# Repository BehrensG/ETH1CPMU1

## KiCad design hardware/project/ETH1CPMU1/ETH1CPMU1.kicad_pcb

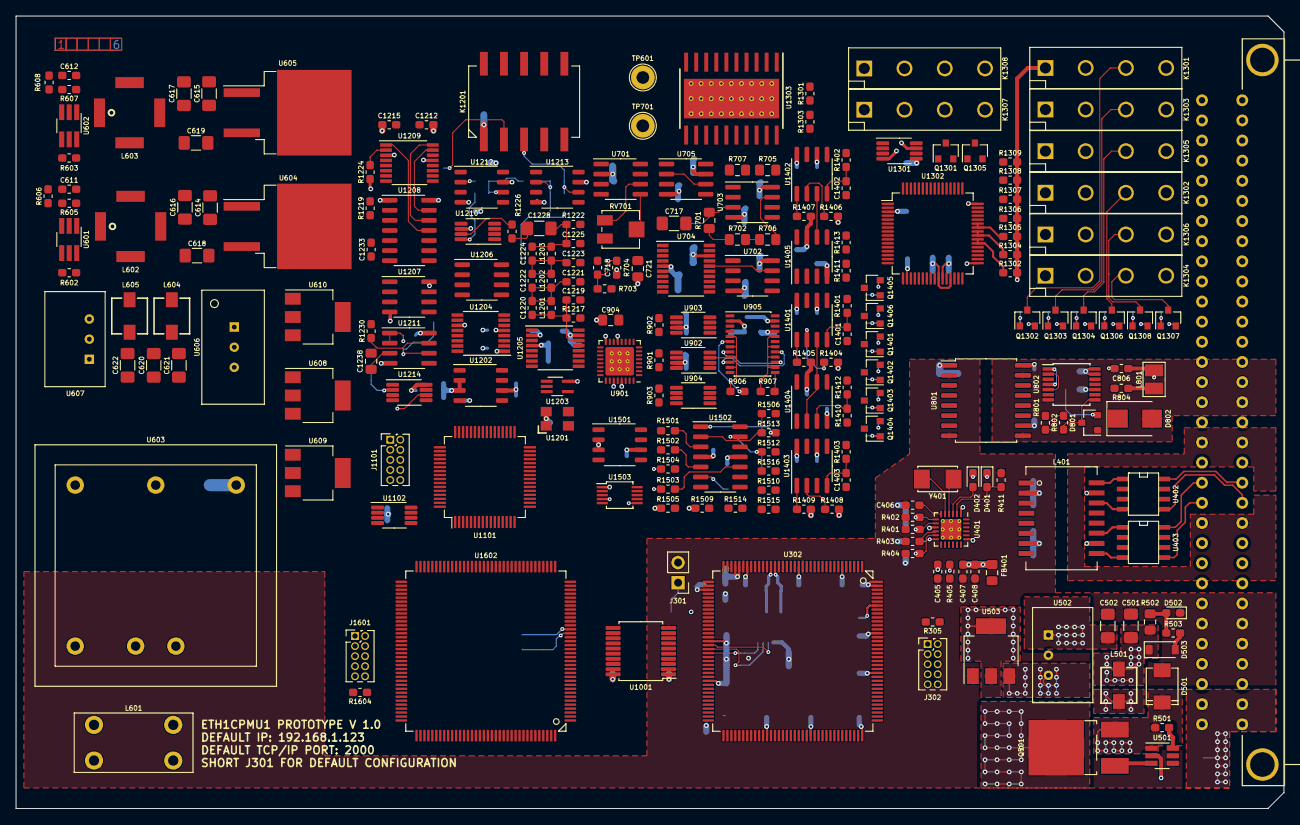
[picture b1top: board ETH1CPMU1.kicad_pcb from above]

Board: 6 copper layers, 160.0 x 100.0 mm, 532 parts (0 on the bottom side), 380 nets.

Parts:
C301, C302, C303, C305, C308, C310, C312, C313, C314, C315, C316, C317, C318, C319, C321, C402, C405, C408, C409, C410, C411, C412, C703, C704, C707, C708, C711, C712, C715, C716, C718, C720, C722, C801, C803, C805, C901, C902, C905, C906, C909, C911, C913, C1001, C1002, C1101, C1102, C1103, C1104, C1105, C1106, C1107, C1109, C1201, C1203, C1204, C1206, C1207, C1208, C1209, C1210, C1212, C1213, C1215, C1216, C1218, C1226, C1227, C1229, C1230, C1231, C1234, C1243, C1301, C1303, C1305, C1310, C1311, C1312, C1316, C1318, C1404, C1405, C1406, C1407, C1408, C1409, C1416, C1417, C1418, C1419, C1501, C1503, C1504, C1601, C1603, C1605, C1608, C1609, C1611, C1612, C1613, C1614, C1615, C1616, C1617, C1619: 100n; C_0603_1608Metric_Pad1.05x0.95mm_HandSolder
C304, C306, C401, C404, C1110, C1111, C1602, C1604: 8p; C_0603_1608Metric_Pad1.05x0.95mm_HandSolder
C307, C309, C1108, C1238, C1606, C1607: 2u2; C_0805_2012Metric_Pad1.15x1.40mm_HandSolder
C311, C320, C406, C407, C605, C606, C802, C804, C1205, C1505, C1610, C1618: 1u; C_0603_1608Metric_Pad1.05x0.95mm_HandSolder
C403, C1233: 470p; C_0603_1608Metric_Pad1.05x0.95mm_HandSolder
C413, C414: 1n/1kV; C_1206_3216Metric_Pad1.42x1.75mm_HandSolder
C501, C502, C620, C621, C622, C623, C624, C625: 10u/50V; C_1206_3216Metric_Pad1.42x1.75mm_HandSolder
C503, C504, C626, C627, C628, C629, C630: 10u/16V; C_1206_3216Metric_Pad1.42x1.75mm_HandSolder
C601, C602, C603, C604, C613, C614, C616, C618, C619: 4u7/50V; C_1206_3216Metric_Pad1.42x1.75mm_HandSolder
C607, C608: 1u/HC; C_1206_3216Metric_Pad1.42x1.75mm_HandSolder
C609, C610: 330p/2kV; C_1206_3216Metric_Pad1.42x1.75mm_HandSolder
C611, C612, C1220: 4p7; C_0603_1608Metric_Pad1.05x0.95mm_HandSolder
C615, C617: 2u2/50V; C_1206_3216Metric_Pad1.42x1.75mm_HandSolder
C701, C702, C705, C706, C709, C710, C713, C714, C719, C721, C903, C904, C907, C908, C910, C912, C917, C1202, C1302, C1304, C1309, C1315, C1317, C1502: 10u; C_0805_2012Metric_Pad1.15x1.40mm_HandSolder
C717, C1228: 10u; C_1206_3216Metric_Pad1.42x1.75mm_HandSolder
C806: 47p; C_0603_1608Metric_Pad1.05x0.95mm_HandSolder
C914, C915, C916, C1217, C1237, C1244, C1307, C1510, C1511, C1512, C1513: 1n; C_0603_1608Metric_Pad1.05x0.95mm_HandSolder
C1211, C1506, C1507, C1508, C1509: 220n; C_0603_1608Metric_Pad1.05x0.95mm_HandSolder
C1214: 10n; C_0603_1608Metric_Pad1.05x0.95mm_HandSolder
C1219, C1225: 22p; C_0603_1608Metric_Pad1.05x0.95mm_HandSolder
C1221, C1223: 56p; C_0603_1608Metric_Pad1.05x0.95mm_HandSolder
C1222: 18p; C_0603_1608Metric_Pad1.05x0.95mm_HandSolder
C1224: 12p; C_0603_1608Metric_Pad1.05x0.95mm_HandSolder
C1232, C1239, C1313, C1314, C1401, C1402, C1403: C; C_0603_1608Metric_Pad1.05x0.95mm_HandSolder
C1235: 330p; C_0603_1608Metric_Pad1.05x0.95mm_HandSolder
C1236: 220p; C_0603_1608Metric_Pad1.05x0.95mm_HandSolder
C1240: 150p; C_0603_1608Metric_Pad1.05x0.95mm_HandSolder
C1241: 4n7; C_0603_1608Metric_Pad1.05x0.95mm_HandSolder
C1242, C1319, C1320, C1321, C1322, C1323, C1324, C1325, C1326, C1410, C1411, C1412, C1413, C1414, C1415: 10p; C_0603_1608Metric_Pad1.05x0.95mm_HandSolder
C1306: 100p; C_0603_1608Metric_Pad1.05x0.95mm_HandSolder
C1308: 3n3; C_0603_1608Metric_Pad1.05x0.95mm_HandSolder
D401: YELLOW; LED_0603_1608Metric_Pad1.05x0.95mm_HandSolder
D402: GREEN; LED_0603_1608Metric_Pad1.05x0.95mm_HandSolder
D501: SM6T30AY; DO_214AA_REV
D502: RED; LED_0603_1608Metric_Pad1.05x0.95mm_HandSolder
D503: MMSZ5249B; D_SOD-123
D601, D602: PMEG6010CEJ; D_SOD-323_HandSoldering
D801: BAV99; SOT-23
D802: SMBJ5.0A; D_SMB
D803: SD36C-01FTG; D_SOD-323_HandSoldering
D1201: SD103ATW; SOT-363_SC-70-6
D1202: 1N4148W; D_SOD-123
F501: MF-LSMF185/33X; Fuse_SMD2920
FB301, FB401, FB1601: 742792031; L_0805_2012Metric_Pad1.15x1.40mm_HandSolder
J201: C64AC; Socket_DIN41612-CaseC1-AC-Male-64Pin-2rows
J301: Conn_02x01; PinHeader_1x02_P2.54mm_Vertical
J302, J1101, J1601: Conn_02x05; PinHeader_2x05_P1.27mm_Vertical
K1201: TQ2SA-5V; SA
K1301, K1302, K1303, K1304, K1305, K1306, K1307, K1308: HE3621A0510; HE360_x-5050462-8
L401: 749010012A
L501, L604, L605: TCK-141
L601: 7448013501
L602, L603: 74489440068
L801: CW252016-R33G; CW252016
L1201, L1202, L1203: 4u7; L_0603_1608Metric_Pad1.05x0.95mm_HandSolder
Q501: IRFR5410; TO-252-2_Rectifier
Q1201, Q1301, Q1302, Q1303, Q1304, Q1305, Q1306, Q1307, Q1308, Q1401, Q1402, Q1403, Q1404, Q1405, Q1406: BC847; SOT-23
R301, R302, R1101, R1102, R1601, R1602: 4k7; R_0603_1608Metric_Pad1.05x0.95mm_HandSolder
R303, R304, R305, R403, R406, R407, R408, R409, R411, R704, R1103, R1104, R1201, R1205, R1209, R1219, R1221, R1223, R1224, R1225, R1227, R1228, R1229, R1230, R1233, R1241, R1242, R1243, R1244, R1310, R1311, R1312, R1313, R1314, R1315, R1316, R1317, R1414, R1415, R1416, R1417, R1418, R1419, R1603, R1604: 10k; R_0603_1608Metric_Pad1.05x0.95mm_HandSolder
R401, R402, R404, R405: 33; R_0603_1608Metric_Pad1.05x0.95mm_HandSolder
R410: 1k5; R_0603_1608Metric_Pad1.05x0.95mm_HandSolder
R412: 12k1; R_0603_1608Metric_Pad1.05x0.95mm_HandSolder
R413, R414: 270; R_0603_1608Metric_Pad1.05x0.95mm_HandSolder
R415, R416, R417, R418: 49R9; R_0603_1608Metric_Pad1.05x0.95mm_HandSolder
R419: 1M/1kV; R_1206_3216Metric_Pad1.42x1.75mm_HandSolder
R420, R421: 75/1%; R_0603_1608Metric_Pad1.05x0.95mm_HandSolder
R501, R1216, R1404, R1405, R1406, R1407, R1408, R1409, R1412, R1413, R1513, R1514, R1515, R1516: 100k; R_0603_1608Metric_Pad1.05x0.95mm_HandSolder
R502: 6k8/0.5W; R_0805_2012Metric_Pad1.15x1.40mm_HandSolder
R503: 370; R_0603_1608Metric_Pad1.05x0.95mm_HandSolder
R601, R603, R605, R607: 1M; R_0603_1608Metric_Pad1.05x0.95mm_HandSolder
R602, R604: 287k; R_0603_1608Metric_Pad1.05x0.95mm_HandSolder
R606, R608, R1202, R1203, R1204, R1226, R1231, R1236, R1237, R1239, R1309, R1401, R1402, R1403: R; R_0603_1608Metric_Pad1.05x0.95mm_HandSolder
R701: 1k5/0.01%/0.6ppm; R_0805_2012Metric_Pad1.15x1.40mm_HandSolder
R702, R705, R707: 1k/0.01%/0.6ppm; R_0805_2012Metric_Pad1.15x1.40mm_HandSolder
R703, R904, R905, R906, R907, R1206, R1218: 0; R_0603_1608Metric_Pad1.05x0.95mm_HandSolder
R706: 2k/0.01%/0.6ppm; R_0805_2012Metric_Pad1.15x1.40mm_HandSolder
R801: 14k7; R_0603_1608Metric_Pad1.05x0.95mm_HandSolder
R802, R901, R902, R903: 100; R_0603_1608Metric_Pad1.05x0.95mm_HandSolder
R803, R1212, R1501, R1502, R1503, R1504: 1k; R_0603_1608Metric_Pad1.05x0.95mm_HandSolder
R804: 47; R_0603_1608Metric_Pad1.05x0.95mm_HandSolder
R805: 51R1; R_0603_1608Metric_Pad1.05x0.95mm_HandSolder
R1207: 4k22; R_0603_1608Metric_Pad1.05x0.95mm_HandSolder
R1208, R1213: 3k9; R_0603_1608Metric_Pad1.05x0.95mm_HandSolder
R1210, R1211: 1k96; R_0603_1608Metric_Pad1.05x0.95mm_HandSolder
R1214, R1505, R1507, R1509, R1511: 24k9; R_0603_1608Metric_Pad1.05x0.95mm_HandSolder
R1215, R1506, R1508, R1510, R1512: 33k2; R_0603_1608Metric_Pad1.05x0.95mm_HandSolder
R1217, R1222: 300; R_0603_1608Metric_Pad1.05x0.95mm_HandSolder
R1220: 70k; R_0603_1608Metric_Pad1.05x0.95mm_HandSolder
R1232, R1235, R1238: 6k81; R_0603_1608Metric_Pad1.05x0.95mm_HandSolder
R1234: 237k; R_0603_1608Metric_Pad1.05x0.95mm_HandSolder
R1240: 619; R_0603_1608Metric_Pad1.05x0.95mm_HandSolder
R1301, R1303: 5k1; R_0603_1608Metric_Pad1.05x0.95mm_HandSolder
R1302: 124k; R_0603_1608Metric_Pad1.05x0.95mm_HandSolder
R1304: 12k4; R_0603_1608Metric_Pad1.05x0.95mm_HandSolder
R1305: 1k24; R_0603_1608Metric_Pad1.05x0.95mm_HandSolder
R1306: 124; R_0603_1608Metric_Pad1.05x0.95mm_HandSolder
R1307: 12R4; R_0603_1608Metric_Pad1.05x0.95mm_HandSolder
R1308: 3R16; R_0603_1608Metric_Pad1.05x0.95mm_HandSolder
R1410, R1411: 50; R_0603_1608Metric_Pad1.05x0.95mm_HandSolder
RV701: 3314J-1-103E; Potentiometer_Bourns_3314J_Vertical
TP601, TP701: 5006; TestPoint_Loop_D2.60mm_Drill1.6mm_Beaded
U301, U1102, U1601: 24LC08B-E/MS; MSOP-8_3x3mm_P0.65mm
U302: STM32F765ZGT6; TQFP-144_20x20mm_P0.5mm
U401: LAN8742A; QFN-24-1EP_4x4mm_P0.5mm_EP2.6x2.6mm_ThermalVias
U402, U403: LC03-3.3; SO8E
U501: MAX5902; SOT-23-6_Handsoldering
U502: TSR1-2450; TSR1
U503, U608, U609: LM1117IMP-3.3/NOPB; SOT-223-3_TabPin2
U601, U602: LT8330_S6; TSOT-23-6_HandSoldering
U603: THL15-2415WI; THL15
U604: MC7815BD2TG; TO-263-2
U605: MC7915BD2TG; TO-263-2
U606: TSR2-2450; TSR2
U607: TSR1-2490; TSR1
U610: LM1117IMP-5.0/NOPB; SOT-223-3_TabPin2
U701: REF02AU; SOIC-8_3.9x4.9mm_P1.27mm
U702, U703: AD8676; SOIC-8_3.9x4.9mm_P1.27mm
U704: AD5791; TSSOP-20_4.4x6.5mm_P0.65mm
U705: AD8675; SOIC-8_3.9x4.9mm_P1.27mm
U801: ADuM5402; SOIC-16W_7.5x10.3mm_P1.27mm
U802: 74AC125; TSSOP-14_4.4x5mm_P0.65mm
U901: ADS8363; QFN-32-1EP_5x5mm_P0.5mm_EP3.6x3.6mm_ThermalVias
U902, U903, U904: INA159; MSOP-8_3x3mm_P0.65mm
U905: ADG1414BRU; TSSOP-24_4.4x7.8mm_P0.65mm
U1001: ADuM3151; SSOP-20_5.3x7.2mm_P0.65mm
U1101: STM32F413RGT6Tx; LQFP-64_10x10mm_P0.5mm
U1201: ECS-3225SMV-500-GP-TR; ECS
U1202, U1501: REF192; SSOP-8_3.9x5.05mm_P1.27mm
U1203: 74AHCT1G08; SOT-353_SC-70-5_Handsoldering
U1204: AD5689BRUZ; TSSOP-16_4.4x5mm_P0.65mm
U1205: AD9835; TSSOP-16_4.4x5mm_P0.65mm
U1206, U1207, U1211: TL072; SOIC-8_3.9x4.9mm_P1.27mm
U1208: TXB0104D; SOIC-14_3.9x8.7mm_P1.27mm
U1209: DG408DY; TSSOP-16_4.4x5mm_P0.65mm
U1210: AD5453YRMZ; MSOP-8_3x3mm_P0.65mm
U1212, U1213: LT1468; SSOP-8_3.9x5.05mm_P1.27mm
U1214: ADS7818; MSOP-8_3x3mm_P0.65mm
U1301: DG419LEUA; MSOP-8_3x3mm_P0.65mm
U1302: AD5520; LQFP-64_10x10mm_P0.5mm
U1303: THS6012; PowerPAD
U1401, U1402, U1403: PGA103; SOIC-8_3.9x4.9mm_P1.27mm
U1404, U1405: OPA602; SOIC-8_3.9x4.9mm_P1.27mm
U1502: TL074; SOIC-14_3.9x8.7mm_P1.27mm
U1503: AD5324; MSOP-10_3x3mm_P0.5mm
U1602: STM32H743ZI; TQFP-144_20x20mm_P0.5mm
Y301, Y1101, Y1601: NX3225GD-8MHZ-STD-CRA-3; NX3225GD
Y401: NX5032GA-25.000M-LN-CD-1; NX5032GA

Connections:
+3.3VF: C629.1, C721.1, C722.1, C902.1, C904.1, C906.1, C908.1, C1002.1, C1305.1, C1309.1, C1310.1, C1504.1, C1601.1, C1603.1, C1605.1, C1608.1, C1609.1, C1610.1, C1611.1, C1612.1, C1613.1, C1614.1, C1615.1, C1616.1, C1617.1, FB1601.2, J1601.1, R704.1, R1601.1, R1602.1, R1604.1, U609.2, U704.9, U704.10, U901.16, U901.27, U905.23, U1001.20, U1301.5, U1302.3, U1302.18, U1503.1, U1601.8, U1602.6, U1602.17, U1602.30, U1602.39, U1602.52, U1602.62, U1602.72, U1602.84, U1602.95, U1602.108, U1602.121, U1602.131, U1602.143, U1602.144
+3.3VP: C628.1, C1101.1, C1102.1, C1103.1, C1104.1, C1105.1, C1106.1, C1107.1, C1201.1, C1203.1, C1204.1, J1101.1, R1101.1, R1102.1, R1104.2, R1201.1, R1203.1, R1205.1, R1209.1, R1228.1, U608.2, U1101.1, U1101.13, U1101.19, U1101.32, U1101.48, U1101.64, U1102.8, U1201.1, U1201.4, U1203.5, U1204.11, U1205.4, U1208.1, U1210.6
+3V3: C301.1, C302.1, C303.1, C305.1, C308.1, C310.1, C311.1, C312.1, C313.1, C314.1, C315.1, C316.1, C317.1, C318.1, C319.1, C402.1, C405.1, C504.1, C801.1, C802.1, C1001.1, FB301.2, FB401.2, J302.1, R301.1, R302.1, R303.2, R305.1, R406.1, R407.1, R408.1, R409.1, R410.1, U301.8, U302.6, U302.17, U302.30, U302.39, U302.52, U302.62, U302.72, U302.84, U302.95, U302.108, U302.121, U302.131, U302.143, U302.144, U401.9, U503.2, U801.1, U1001.1
+5V: C503.1, U502.3, U503.3
+5VF: C630.1, C909.1, C910.1, C911.1, C912.1, C913.1, C917.1, C1202.1, C1206.1, C1207.1, C1208.1, C1214.1, C1243.1, C1502.1, D1202.1, K1201.1, K1301.2, K1302.2, K1303.2, K1304.2, K1305.2, K1306.2, K1307.2, K1308.2, R1224.2, R1243.1, U610.2, U901.13, U901.29, U902.7, U903.7, U904.7, U1202.2, U1202.3, U1204.5, U1205.15, U1208.14, U1214.8, U1501.2, U1501.3
+5V_TRIG: C803.1, C804.1, C805.1, R803.1, U801.10, U801.16, U802.13, U802.14
+15VF: C618.1, C701.1, C702.1, C703.1, C704.1, C709.1, C710.1, C711.1, C712.1, C719.1, C720.1, C905.1, C907.1, C1209.1, C1212.1, C1226.1, C1229.1, C1303.1, C1304.1, C1311.1, C1315.1, C1316.1, C1404.1, C1405.1, C1406.1, C1416.1, C1418.1, C1501.1, R1404.2, R1405.2, R1406.2, R1407.2, R1408.2, R1409.2, U604.3, U701.2, U702.8, U703.8, U704.5, U705.7, U905.2, U1206.8, U1207.8, U1209.13, U1211.8, U1212.7, U1213.7, U1301.4, U1302.27, U1302.33, U1302.50, U1303.3, U1303.18, U1401.8, U1402.8, U1403.8, U1404.7, U1405.7, U1502.4
+24V: F501.2, J201.A31, J201.A32, J201.C31, J201.C32
+24VDD: C501.1, C601.1, C604.1, D503.1, L501.1, L601.2, Q501.2, R502.1, U501.2
+24VF: C602.1, C603.1, C613.1, C620.1, C621.1, C622.1, L602.1, L603.1, L604.1, L605.1, R601.1, R603.1, U601.6, U602.6, U603.3
-15VF: C619.1, C705.1, C706.1, C707.1, C708.1, C713.1, C714.1, C715.1, C716.1, C901.1, C903.1, C1215.1, C1218.1, C1227.1, C1231.1, C1234.1, C1301.1, C1302.1, C1312.1, C1317.1, C1318.1, C1407.1, C1408.1, C1409.1, C1417.1, C1419.1, C1503.1, U605.3, U702.4, U703.4, U704.18, U705.4, U905.21, U1206.4, U1207.4, U1209.3, U1211.4, U1212.4, U1213.4, U1301.7, U1302.26, U1302.29, U1302.48, U1303.1, U1303.20, U1401.6, U1402.6, U1403.6, U1404.4, U1405.4, U1502.11
/AC source/+2V5REF: C1205.1, R1207.2, R1214.2, U1202.6, U1204.1
/AC source/AC_FOURCE: K1201.4, U905.10, U905.17, U1301.8
/AC source/AC_RELAY: D1202.2, K1201.10, Q1201.3, R1241.1, U1101.37
/AC source/DDS_DAC_RSTSEL: R1202.2, U1101.14
/AC source/DDS_DAC_SCLK: U1101.21, U1204.12
/AC source/DDS_DAC_SDIN: U1101.23, U1204.14
/AC source/DDS_DAC_SDO: U1101.22, U1204.8
/AC source/DDS_DAC_~LDAC: U1101.16, U1204.9
/AC source/DDS_DAC_~RESET: R1205.2, U1101.17, U1204.15
/AC source/DDS_DAC_~SYNC: R1201.2, U1101.50, U1204.13
/AC source/DDS_FGEN_FSELECT: U1101.28, U1205.10
/AC source/DDS_FGEN_PSEL0: U1101.41, U1205.12
/AC source/DDS_FGEN_PSEL1: U1101.42, U1205.11
/AC source/DDS_FGEN_SCLK: U1101.26, U1205.7
/AC source/DDS_FGEN_SDATA: U1101.43, U1205.8
/AC source/DDS_FGEN_~FSYNC: R1209.2, U1101.27, U1205.9
/AC source/DDS_MDAC_DIN: U1101.15, U1210.4
/AC source/DDS_MDAC_SCLK: U1101.34, U1210.3
/AC source/DDS_MDAC_~SYNC: U1101.33, U1210.5
/AC source/DDS_MEAS_A0: U1101.38, U1208.4
/AC source/DDS_MEAS_A1: U1101.39, U1208.3
/AC source/DDS_MEAS_A2: U1101.40, U1208.2
/AC source/DDS_MEAS_CLK: U1101.29, U1214.7
/AC source/DDS_MEAS_CONV: U1101.62, U1214.5
/AC source/DDS_MEAS_DATA: R1244.1, U1101.11
/AC source/MEAS_AMPL: R1219.1, U1209.5
/AC source/MEAS_OUT: C1244.1, R1220.2, R1242.1
/AC source/V_AMPL: C1216.1, R1207.1, R1208.2, R1218.1, U1205.2
/AC source/V_OFFSET: C1217.1, R1216.1, R1236.2, U1206.7
/ADC/ADC_BUSY: U901.23, U1602.45
/ADC/ADC_CLOCK: U901.22, U1602.41
/ADC/ADC_CONVST: U901.19, U1602.46
/ADC/ADC_MUX_DIN: U905.3, U1602.76
/ADC/ADC_MUX_SCLK: U905.1, U1602.69
/ADC/ADC_MUX_SDO: U905.22, U1602.75
/ADC/ADC_MUX_~SYNC: U905.24, U1602.73
/ADC/ADC_RD: U901.20, U1602.44
/ADC/ADC_SDI: U901.18, U1602.43
/ADC/ADC_SDOA: U901.25, U1602.42
/ADC/ADC_~CS: U901.21, U1602.40
/ADC/DC_FOURCE: U705.2, U705.6, U905.8, U905.15, U1301.2
/ADC/PMU_MEASI_GAIN: R907.1, U905.13, U1402.7
/ADC/PMU_MEASV_GAIN: R906.2, U905.6, U1401.7
/ADC/PMU_MEAS_GAIN: U903.3, U1403.7
/Connector/A: J201.A2, J201.C2, K1302.4
/Connector/B: J201.A3, J201.C3, K1303.4
/Connector/C: J201.A4, J201.A5, J201.C4, J201.C5, K1305.4
/Connector/E: J201.A6, J201.C6, K1306.4
/Connector/EXT_TRIG: C806.1, D803.1, J201.A16, L801.1
/Connector/F: J201.A7, J201.C7, K1301.4, K1304.4
/Connector/RX+: J201.A20, U403.8
/Connector/RX-: J201.A21, U403.5
/Connector/TX+: J201.C20, U402.8
/Connector/TX-: J201.C21, U402.5
/DAC/+2V5REF: C1505.1, R1505.2, R1507.2, R1509.2, R1511.2, U1501.6, U1503.5
/DAC/DAC_DIN: U1503.8, U1602.113
/DAC/DAC_SCLK: U1503.9, U1602.111
/DAC/DAC_~SYNC: U1503.10, U1602.110
/DAC/OFFSET1: C1512.1, R1412.1, R1515.1, U1502.8
/DAC/OFFSET2: C1513.1, R1413.1, R1516.1, U1502.14
/DAC/PMU_CLH: C1511.1, R1514.1, U1302.63, U1502.7
/DAC/PMU_CPH: C1510.1, R1513.1, U1302.1, U1502.1
/DC source/DC_DAC_SCLK: R703.2, U704.13, U1602.19
/DC source/DC_DAC_SDIN: U704.12, U1602.21
/DC source/DC_DAC_SDO: U704.11, U1602.20
/DC source/DC_DAC_~CLR: U704.7, U1602.14
/DC source/DC_DAC_~LDAC: U704.8, U1602.15
/DC source/DC_DAC_~SYNC: U704.14, U1602.18
/Ethernet/ETH_RXN: L401.8, R418.2, U401.22
/Ethernet/ETH_RXP: L401.6, R417.2, U401.23
/Ethernet/ETH_TXN: L401.3, R416.2, U401.20
/Ethernet/ETH_TXP: L401.1, R415.2, U401.21
/Ethernet/MODE0: R401.1, R406.2, U401.8
/Ethernet/MODE1: R402.1, R407.2, U401.7
/Ethernet/MODE2: R404.1, R408.2, U401.11
/Ethernet/NRST: C321.1, J302.10, R305.2, U302.25, U401.15
/Ethernet/REFCLK0: R405.1, R409.2, U401.14
/Ethernet/REF_CLK: R405.2, U302.35
/Ethernet/RMII_CRS_DV: R404.2, U302.43
/Ethernet/RMII_MDC: U302.27, U401.13
/Ethernet/RMII_MDIO: R410.2, U302.36, U401.12
/Ethernet/RMII_RXD0: R401.2, U302.44
/Ethernet/RMII_RXD1: R402.2, U302.45
/Ethernet/RMII_TXD0: U302.128, U401.17
/Ethernet/RMII_TXD1: U302.129, U401.18
/Ethernet/RMII_TXEN: U302.126, U401.16
/Isolation/MCU1_GPIO_OUT1: U302.22, U1001.7
/Isolation/MCU1_GPIO_OUT2: U302.26, U1001.8
/Isolation/MCU1_MCLK: U302.19, U1001.3
/Isolation/MCU1_MISO: U302.20, U1001.5
/Isolation/MCU1_MOSI: U302.21, U1001.4
/Isolation/MCU1_STATUS_IN: U302.28, U1001.9
/Isolation/MCU1_~MSS: U302.18, U1001.6
/Isolation/MCU2_GPIO_OUT1: U1001.14, U1602.7
/Isolation/MCU2_GPIO_OUT2: U1001.13, U1602.8
/Isolation/MCU2_MISO: U1001.16, U1602.4
/Isolation/MCU2_MOSI: U1001.17, U1602.5
/Isolation/MCU2_SCLK: U1001.18, U1602.1
/Isolation/MCU2_STATUS_IN: U1001.12, U1602.9
/Isolation/MCU2_~SSS: U1001.15, U1602.3
/MCU1/EEPROM_SCL: R302.2, U301.6, U302.54
/MCU1/EEPROM_SDA: R301.2, U301.5, U302.55
/MCU1/EEPROM_WP: U301.7, U302.53
/MCU1/MCU_DEFAULT: J301.1, R303.1, U302.104
/MCU1/MCU_VDDA: C320.1, FB301.1, U302.32, U302.33
/MCU1/TCK_SWCLK: J302.4, U302.109
/MCU1/TDI: J302.8, U302.110
/MCU1/TDO: J302.6, U302.133
/MCU1/TMS_SWDIO: J302.2, U302.105
/MCU1/TRIG_EN: U302.74, U801.3
/MCU1/TRIG_IN: U302.76, U801.5
/MCU1/TRIG_OUT: U302.75, U801.4
/MCU2/EEPROM_SCL: R1602.2, U1601.6, U1602.54
/MCU2/EEPROM_SDA: R1601.2, U1601.5, U1602.55
/MCU2/EEPROM_WP: U1601.7, U1602.53
/MCU2/FOURCE_SELECT: U1301.6, U1602.68
/MCU2/G1A0_CTR: R1415.1, U1602.114
/MCU2/G1A1_CTR: R1414.1, U1602.115
/MCU2/G2A0_CTR: R1419.1, U1602.116
/MCU2/G2A1_CTR: R1418.1, U1602.117
/MCU2/G3A0_CTR: R1417.1, U1602.118
/MCU2/G3A1_CTR: R1416.1, U1602.119
/MCU2/MCU3_MISO: U1101.52, U1602.124
/MCU2/MCU3_MOSI: U1101.53, U1602.123
/MCU2/MCU3_NSS: U1101.20, U1602.125
/MCU2/MCU3_SCLK: U1101.51, U1602.126
/MCU2/MCU_NRST: C1619.1, J1601.10, R1604.2, U1602.25
/MCU2/MCU_VDDA: C1618.1, FB1601.1, U1602.32, U1602.33
/MCU2/PMU_AC0: U1302.15, U1602.60
/MCU2/PMU_AC1: U1302.16, U1602.63
/MCU2/PMU_AM0: U1302.21, U1602.82
/MCU2/PMU_AM1: U1302.20, U1602.85
/MCU2/PMU_AM2: U1302.19, U1602.86
/MCU2/PMU_CLHDETECT: U1302.8, U1602.66
/MCU2/PMU_CLLDETECT: U1302.9, U1602.67
/MCU2/PMU_CPCK: U1302.6, U1602.79
/MCU2/PMU_CPOH: U1302.4, U1602.64
/MCU2/PMU_CPOL: U1302.5, U1602.65
/MCU2/PMU_CPSEL: U1302.25, U1602.58
/MCU2/PMU_MSEL: U1302.24, U1602.59
/MCU2/PMU_STANDBY: U1302.22, U1602.77
/MCU2/PMU_~CS: U1302.13, U1602.81
/MCU2/PMU_~MOE: U1302.12, U1302.23, U1602.80
/MCU2/PMU_~STB: U1302.14, U1602.78
/MCU2/R_GND: R1317.1, U1602.90
/MCU2/R_GUARD: R1313.1, U1602.93
/MCU2/R_GUARDIN: R1316.1, U1602.89
/MCU2/R_MEASHV: R1315.1, U1602.88
/MCU2/R_MEASIL: R1311.1, U1602.91
/MCU2/R_MEASVL: R1312.1, U1602.92
/MCU2/TCK_SWCLK: J1601.4, U1602.109
/MCU2/TMS_SWDIO: J1601.2, U1602.105
/MCU3/EEPROM_SCL: R1102.2, U1101.58, U1102.6
/MCU3/EEPROM_SDA: R1101.2, U1101.59, U1102.5
/MCU3/EEPROM_WP: U1101.57, U1102.7
/MCU3/MCU_NRST: C1109.1, J1101.10, R1104.1, U1101.7
/MCU3/TCK_SWCLK: J1101.4, U1101.49
/MCU3/TMS_SWDIO: J1101.2, U1101.46
/PGA/GAIN1A0: Q1402.3, R1405.1, U1401.1
/PGA/GAIN1A1: Q1401.3, R1404.1, U1401.2
/PGA/GAIN2A0: Q1406.3, R1407.1, U1402.1
/PGA/GAIN2A1: Q1405.3, R1406.1, U1402.2
/PGA/GAIN3A0: Q1404.3, R1409.1, U1403.1
/PGA/GAIN3A1: Q1403.3, R1408.1, U1403.2
/PGA/PMU_MEASIOUT: R1402.2, U1302.60
/PGA/PMU_MEASOUT: R1403.2, U1302.58
/PGA/PMU_MEASVOUT: R1401.2, U1302.61
/PMU/PMU_QM4: R1314.1, U1302.10
/PMU/PMU_QM5: R1310.1, U1302.11
/Trigger/EXT_TRIG_SIGN: R801.1, U801.12, U802.11
/Trigger/TRIG_OUT_EN: U801.14, U802.1, U802.4, U802.10
/Trigger/TRIG_OUT_SIGN: U801.13, U802.2, U802.5, U802.9
AGNDF: C602.2, C603.2, C605.2, C606.2, C609.1, C610.1, C613.2, C614.2, C615.2, C616.2, C617.2, C618.2, C619.2, C620.2, C621.2, C622.2, C623.2, C624.2, C625.2, C626.2, C627.2, C628.2, C629.2, C630.2, C701.2, C702.2, C703.2, C704.2, C705.2, C706.2, C707.2, C708.2, C709.2, C710.2, C711.2, C712.2, C713.2, C714.2, C715.2, C716.2, C717.2, C718.2, C719.2, C720.2, C721.2, C722.2, C901.2, C902.2, C903.2, C904.2, C905.2, C906.2, C907.2, C908.2, C909.2, C910.2, C911.2, C912.2, C913.2, C914.2, C915.2, C916.2, C917.2, C1002.2, C1101.2, C1102.2, C1103.2, C1104.2, C1105.2, C1106.2, C1107.2, C1108.1, C1109.2, C1110.2, C1111.2, C1201.2, C1202.2, C1203.2, C1204.2, C1205.2, C1206.2, C1207.2, C1208.2, C1209.2, C1211.2, C1212.2, C1213.1, C1215.2, C1216.2, C1218.2, C1219.2, C1221.2, C1223.2, C1225.2, C1226.2, C1227.2, C1229.2, C1231.2, C1233.2, C1234.2, C1235.2, C1238.2, C1240.2, C1241.2, C1242.2, C1243.2, C1244.2, C1301.2, C1302.2, C1303.2, C1304.2, C1305.2, C1309.2, C1310.2, C1311.2, C1312.2, C1315.2, C1316.2, C1317.2, C1318.2, C1319.2, C1320.2, C1321.2, C1322.2, C1323.2, C1324.2, C1325.2, C1326.2, C1401.2, C1402.2, C1403.2, C1404.2, C1405.2, C1406.2, C1407.2, C1408.2, C1409.2, C1410.2, C1411.2, C1412.2, C1413.2, C1414.2, C1415.2, C1416.2, C1417.2, C1418.2, C1419.2, C1501.2, C1502.2, C1503.2, C1504.2, C1505.2, C1506.2, C1507.2, C1508.2, C1509.2, C1601.2, C1602.2, C1603.2, C1604.2, C1605.2, C1606.2, C1607.2, C1608.2, C1609.2, C1610.2, C1611.2, C1612.2, C1613.2, C1614.2, C1615.2, C1616.2, C1617.2, C1618.2, C1619.2, D601.1, J1101.3, J1101.5, J1601.3, J1601.5, K1201.7, K1201.8, K1201.9, K1306.1, L602.3, Q1201.2, Q1301.2, Q1302.2, Q1303.2, Q1304.2, Q1305.2, Q1306.2, Q1307.2, Q1308.2, Q1401.2, Q1402.2, Q1403.2, Q1404.2, Q1405.2, Q1406.2, R602.2, R604.2, R606.2, R608.2, R705.1, R904.1, R905.1, R1103.2, R1204.2, R1208.1, R1213.2, R1215.2, R1217.2, R1221.2, R1222.2, R1223.2, R1410.2, R1411.2, R1506.2, R1508.2, R1510.2, R1512.2, R1603.2, RV701.3, TP601.1, U601.2, U602.2, U603.5, U604.2, U605.1, U606.2, U607.2, U608.1, U609.1, U610.1, U701.4, U703.5, U704.15, U704.19, U901.11, U901.12, U901.17, U901.28, U901.30, U901.33, U902.2, U902.4, U903.2, U903.4, U904.2, U904.4, U905.4, U905.12, U905.19, U1001.11, U1001.19, U1101.12, U1101.18, U1101.31, U1101.47, U1101.63, U1102.1, U1102.2, U1102.3, U1102.4, U1201.2, U1202.4, U1203.3, U1204.4, U1204.10, U1205.5, U1205.13, U1208.7, U1209.4, U1209.14, U1210.2, U1211.5, U1212.3, U1213.3, U1214.3, U1214.4, U1301.3, U1302.2, U1302.7, U1302.17, U1302.28, U1302.57, U1302.59, U1302.64, U1303.21, U1501.4, U1503.7, U1601.1, U1601.2, U1601.3, U1601.4, U1602.16, U1602.31, U1602.38, U1602.51, U1602.61, U1602.83, U1602.94, U1602.107, U1602.120, U1602.130
Earth: C413.1, C414.2, J201.A18, J201.A22, J201.C18, J201.C22, R419.1
GND: C301.2, C302.2, C303.2, C304.2, C305.2, C306.2, C307.2, C308.2, C309.2, C310.2, C311.2, C312.2, C313.2, C314.2, C315.2, C316.2, C317.2, C318.2, C319.2, C320.2, C321.2, C401.2, C402.2, C403.2, C404.2, C405.2, C406.2, C407.2, C408.2, C409.2, C410.2, C411.2, C412.2, C413.2, C501.2, C502.2, C503.2, C504.2, C601.2, C604.2, C801.2, C802.2, C1001.2, D501.2, D502.1, J201.A27, J201.A28, J201.C27, J201.C28, J301.2, J302.3, J302.5, L601.1, R304.2, R403.2, R411.2, R412.1, R413.2, R414.2, R419.2, U301.1, U301.2, U301.3, U301.4, U302.16, U302.31, U302.38, U302.51, U302.61, U302.83, U302.94, U302.107, U302.120, U302.130, U401.25, U501.4, U502.2, U503.1, U801.2, U801.8, U1001.2, U1001.10
GND_TRIG: C803.2, C804.2, C805.2, D801.1, D802.2, D803.2, J201.C16, R805.2, U801.9, U801.15, U802.7
unnamed: C304.1, U302.23, Y301.1
unnamed: C306.1, U302.24, Y301.2
unnamed: C307.1, U302.71
unnamed: C309.1, U302.106
unnamed: C401.1, U401.5, Y401.2
unnamed: C403.1, C406.1, U401.6
unnamed: C404.1, U401.4, Y401.1
unnamed: C414.1, R420.2, R421.2
unnamed: C502.1, L501.2, U502.1
unnamed: C605.1, U601.5
unnamed: C606.1, U602.5
unnamed: C607.1, D602.2, L602.2
unnamed: C607.2, L602.4, U601.1
unnamed: C608.1, D601.2, L603.2
unnamed: C608.2, L603.4, U602.1
unnamed: C609.2, L601.3, U603.1
unnamed: C610.2, L601.4, U603.2
unnamed: C611.1, C614.1, C616.1, D602.1, R605.1, U604.1
unnamed: C611.2, R605.2, R606.1, U601.3
unnamed: C612.1, C615.1, C617.1, L603.3, R607.1, U605.2
unnamed: C612.2, R607.2, R608.1, U602.3
unnamed: C623.1, C625.1, L604.2, U606.1
unnamed: C624.1, L605.2, U607.1
unnamed: C626.1, U606.3, U608.3, U609.3
unnamed: C627.1, U607.3, U610.3
unnamed: C717.1, R701.1, U703.3
unnamed: C718.1, R703.1, R704.2, U704.6
unnamed: C806.2, R805.1
unnamed: C914.1, R901.1, U902.5, U902.6
unnamed: C915.1, R902.1, U903.5, U903.6
unnamed: C916.1, R903.1, U904.5, U904.6
unnamed: C1108.2, U1101.30
unnamed: C1110.1, U1101.6, Y1101.2
unnamed: C1111.1, U1101.5, Y1101.1
unnamed: C1210.1, R1218.2, R1219.2, U1206.1, U1206.2
unnamed: C1210.2, R1210.1, R1211.2
unnamed: C1211.1, R1212.1, U1206.5
unnamed: C1213.2, D1201.1, D1201.5, R1211.1, U1206.3
unnamed: C1214.2, U1205.16
unnamed: C1217.2, R1214.1, R1215.1, R1216.2, U1206.6
unnamed: C1219.1, C1220.2, L1201.1, R1217.1, U1205.14
unnamed: C1220.1, C1221.1, C1222.2, L1201.2, L1202.1
unnamed: C1222.1, C1223.1, C1224.2, L1202.2, L1203.1
unnamed: C1224.1, C1225.1, C1228.2, L1203.2, R1222.1
unnamed: C1228.1, R1226.2
unnamed: C1230.1, R1227.1, R1230.1, U1211.7
unnamed: C1230.2, R1230.2, R1233.1, U1211.6
unnamed: C1232.1, R1231.1, R1237.2, U1212.6
unnamed: C1232.2, U1210.1, U1212.2
unnamed: C1233.1, C1235.1, R1232.1, R1234.1, R1235.2
unnamed: C1236.1, C1237.1, R1240.2, U1207.6, U1207.7
unnamed: C1236.2, C1237.2, R1235.1, R1238.2
unnamed: C1238.1, U1211.3, U1214.1
unnamed: C1239.1, K1201.3, R1239.1, U1213.6
unnamed: C1239.2, R1236.1, R1237.1, R1239.2, U1213.2
unnamed: C1240.1, R1238.1, U1207.5
unnamed: C1241.1, R1240.1, U1214.2
unnamed: C1242.1, Q1201.1, R1241.2
unnamed: C1306.1, U1302.56
unnamed: C1306.2, U1302.53
unnamed: C1307.1, U1302.55
unnamed: C1307.2, U1302.52
unnamed: C1308.1, U1302.54
unnamed: C1308.2, U1302.51
unnamed: C1313.1, R1302.1, U1302.38, U1302.39
unnamed: C1313.2, K1301.1, R1302.2, R1304.2, R1305.2, R1306.2, R1307.2, R1308.2, R1309.2, U1302.37
unnamed: C1314.1, K1307.1, K1308.1, R1303.1, U1303.2
unnamed: C1314.2, R1303.2, U1303.5
unnamed: C1319.1, Q1301.1, R1310.2
unnamed: C1320.1, Q1302.1, R1311.2
unnamed: C1321.1, Q1303.1, R1312.2
unnamed: C1322.1, Q1304.1, R1313.2
unnamed: C1323.1, Q1305.1, R1314.2
unnamed: C1324.1, Q1306.1, R1315.2
unnamed: C1325.1, Q1307.1, R1316.2
unnamed: C1326.1, Q1308.1, R1317.2
unnamed: C1401.1, R1401.1, U1401.4
unnamed: C1402.1, R1402.1, U1402.4
unnamed: C1403.1, R1403.1, U1403.4
unnamed: C1410.1, Q1401.1, R1414.2
unnamed: C1411.1, Q1402.1, R1415.2
unnamed: C1412.1, Q1403.1, R1416.2
unnamed: C1413.1, Q1404.1, R1417.2
unnamed: C1414.1, Q1405.1, R1418.2
unnamed: C1415.1, Q1406.1, R1419.2
unnamed: C1506.1, R1501.1, U1502.3
unnamed: C1507.1, R1502.1, U1502.5
unnamed: C1508.1, R1503.1, U1502.10
unnamed: C1509.1, R1504.1, U1502.12
unnamed: C1510.2, R1505.1, R1506.1, R1513.2, U1502.2
unnamed: C1511.2, R1507.1, R1508.1, R1514.2, U1502.6
unnamed: C1512.2, R1509.1, R1510.1, R1515.2, U1502.9
unnamed: C1513.2, R1511.1, R1512.1, R1516.2, U1502.13
unnamed: C1602.1, U1602.23, Y1601.1
unnamed: C1604.1, U1602.24, Y1601.2
unnamed: C1606.1, U1602.71
unnamed: C1607.1, U1602.106
unnamed: D401.1, R413.1
unnamed: D401.2, R411.1, U401.2
unnamed: D402.1, R414.1
unnamed: D402.2, U401.3
unnamed: D501.1, F501.1, Q501.3, R501.1, U501.1
unnamed: D502.2, R502.2, R503.2
unnamed: D503.2, R503.1
unnamed: D801.2, D802.1, R803.2
unnamed: D801.3, R802.2, R804.1, U802.3, U802.6, U802.8
unnamed: D1201.2, D1201.6, R1210.2, U1204.3
unnamed: K1201.2, R1242.2
unnamed: K1301.3, Q1302.3
unnamed: K1302.1, U1302.36
unnamed: K1302.3, Q1306.3
unnamed: K1303.1, U1302.34
unnamed: K1303.3, Q1303.3
unnamed: K1304.1, U1302.32
unnamed: K1304.3, Q1307.3
unnamed: K1305.1, U1302.30
unnamed: K1305.3, Q1304.3
unnamed: K1306.3, Q1308.3
unnamed: K1307.3, Q1305.3
unnamed: K1307.4, R1307.1, U1302.46
unnamed: K1308.3, Q1301.3
unnamed: K1308.4, R1308.1, R1309.1, U1302.47
unnamed: L401.9, U403.4
unnamed: L401.10, R420.1
unnamed: L401.11, U403.1
unnamed: L401.14, U402.4
unnamed: L401.15, R421.1
unnamed: L401.16, U402.1
unnamed: L801.2, R804.2
unnamed: Q501.1, U501.3
unnamed: R304.1, U302.138
unnamed: R403.1, U401.10
unnamed: R412.2, U401.24
unnamed: R501.2, U501.6
unnamed: R601.2, R602.1, U601.4
unnamed: R603.2, R604.1, U602.4
unnamed: R701.2, R702.2, RV701.1, TP701.1, U701.6
unnamed: R702.1, R706.2, U703.6
unnamed: R705.2, R707.2, U703.2
unnamed: R706.1, U702.5, U703.7
unnamed: R707.1, U702.3, U703.1
unnamed: R801.2, R802.1, U802.12
unnamed: R901.2, U901.5
unnamed: R902.2, U901.7
unnamed: R903.2, U901.1
unnamed: R904.2, U901.3
unnamed: R905.2, U901.4
unnamed: R906.1, U902.3, U905.5, U905.7, U905.9, U905.11
unnamed: R907.2, U904.3, U905.14, U905.16, U905.18, U905.20
unnamed: R1103.1, U1101.60
unnamed: R1202.1, R1203.2, R1204.1, U1204.16
unnamed: R1206.1, U1203.4, U1205.6
unnamed: R1206.2, U1201.3, U1203.1, U1203.2
unnamed: R1212.2, U1204.7
unnamed: R1213.1, U1205.1
unnamed: R1220.1, R1221.1, U1209.6
unnamed: R1223.1, R1225.2, U1209.7
unnamed: R1224.1, U1209.2
unnamed: R1225.1, R1233.2, R1234.2, U1211.1, U1211.2
unnamed: R1226.1, U1210.7
unnamed: R1227.2, R1229.2, U1207.2
unnamed: R1228.2, U1208.8
unnamed: R1229.1, R1232.2, U1207.1
unnamed: R1231.2, U1210.8
unnamed: R1243.2, R1244.2, U1214.6
unnamed: R1301.1, U1303.4
unnamed: R1301.2, U1302.49
unnamed: R1304.1, U1302.40, U1302.41
unnamed: R1305.1, U1302.42, U1302.43
unnamed: R1306.1, U1302.44, U1302.45
unnamed: R1410.1, R1412.2, U1404.3
unnamed: R1411.1, R1413.2, U1405.3
unnamed: R1501.2, U1503.2
unnamed: R1502.2, U1503.3
unnamed: R1503.2, U1503.4
unnamed: R1504.2, U1503.6
unnamed: R1603.1, U1602.138
unnamed: RV701.2, U701.5
unnamed: U702.1, U704.4
unnamed: U702.2, U704.3
unnamed: U702.6, U704.17
unnamed: U702.7, U704.16
unnamed: U704.2, U705.3
unnamed: U901.6, U901.8, U901.9, U902.1, U902.8, U903.1, U903.8
unnamed: U901.2, U901.10, U904.1, U904.8
unnamed: U1207.3, U1209.8
unnamed: U1208.11, U1209.1
unnamed: U1208.12, U1209.16
unnamed: U1208.13, U1209.15
unnamed: U1301.1, U1302.62
unnamed: U1401.3, U1404.2, U1404.6
unnamed: U1402.3, U1405.2, U1405.6
VCCQ: C407.1, C408.1, C409.1, C410.1, C411.1, C412.1, FB401.1, L401.2, L401.7, R415.1, R416.1, R417.1, R418.1, U401.1, U401.19

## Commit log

2019-11-15 Schematic design
2019-11-20 Function generator schematic design.
2019-11-21 Function generator schematic development.
2019-11-21 Power schematic update.
2019-11-22 New footprint development, changes in schematics.
2019-11-24 Schematic and PCB design.
2019-12-01 PCB design.
2019-12-01 PCB design
2019-12-29 PCB designed
2019-12-29 PCB design done. Need to review.
2020-01-04 Added two analog switches
2020-01-05 Changed distances for fills and added voltage level IC.
2020-01-11 Added summing op amp.
2020-01-11 Fixed problems with references to 3D models.
